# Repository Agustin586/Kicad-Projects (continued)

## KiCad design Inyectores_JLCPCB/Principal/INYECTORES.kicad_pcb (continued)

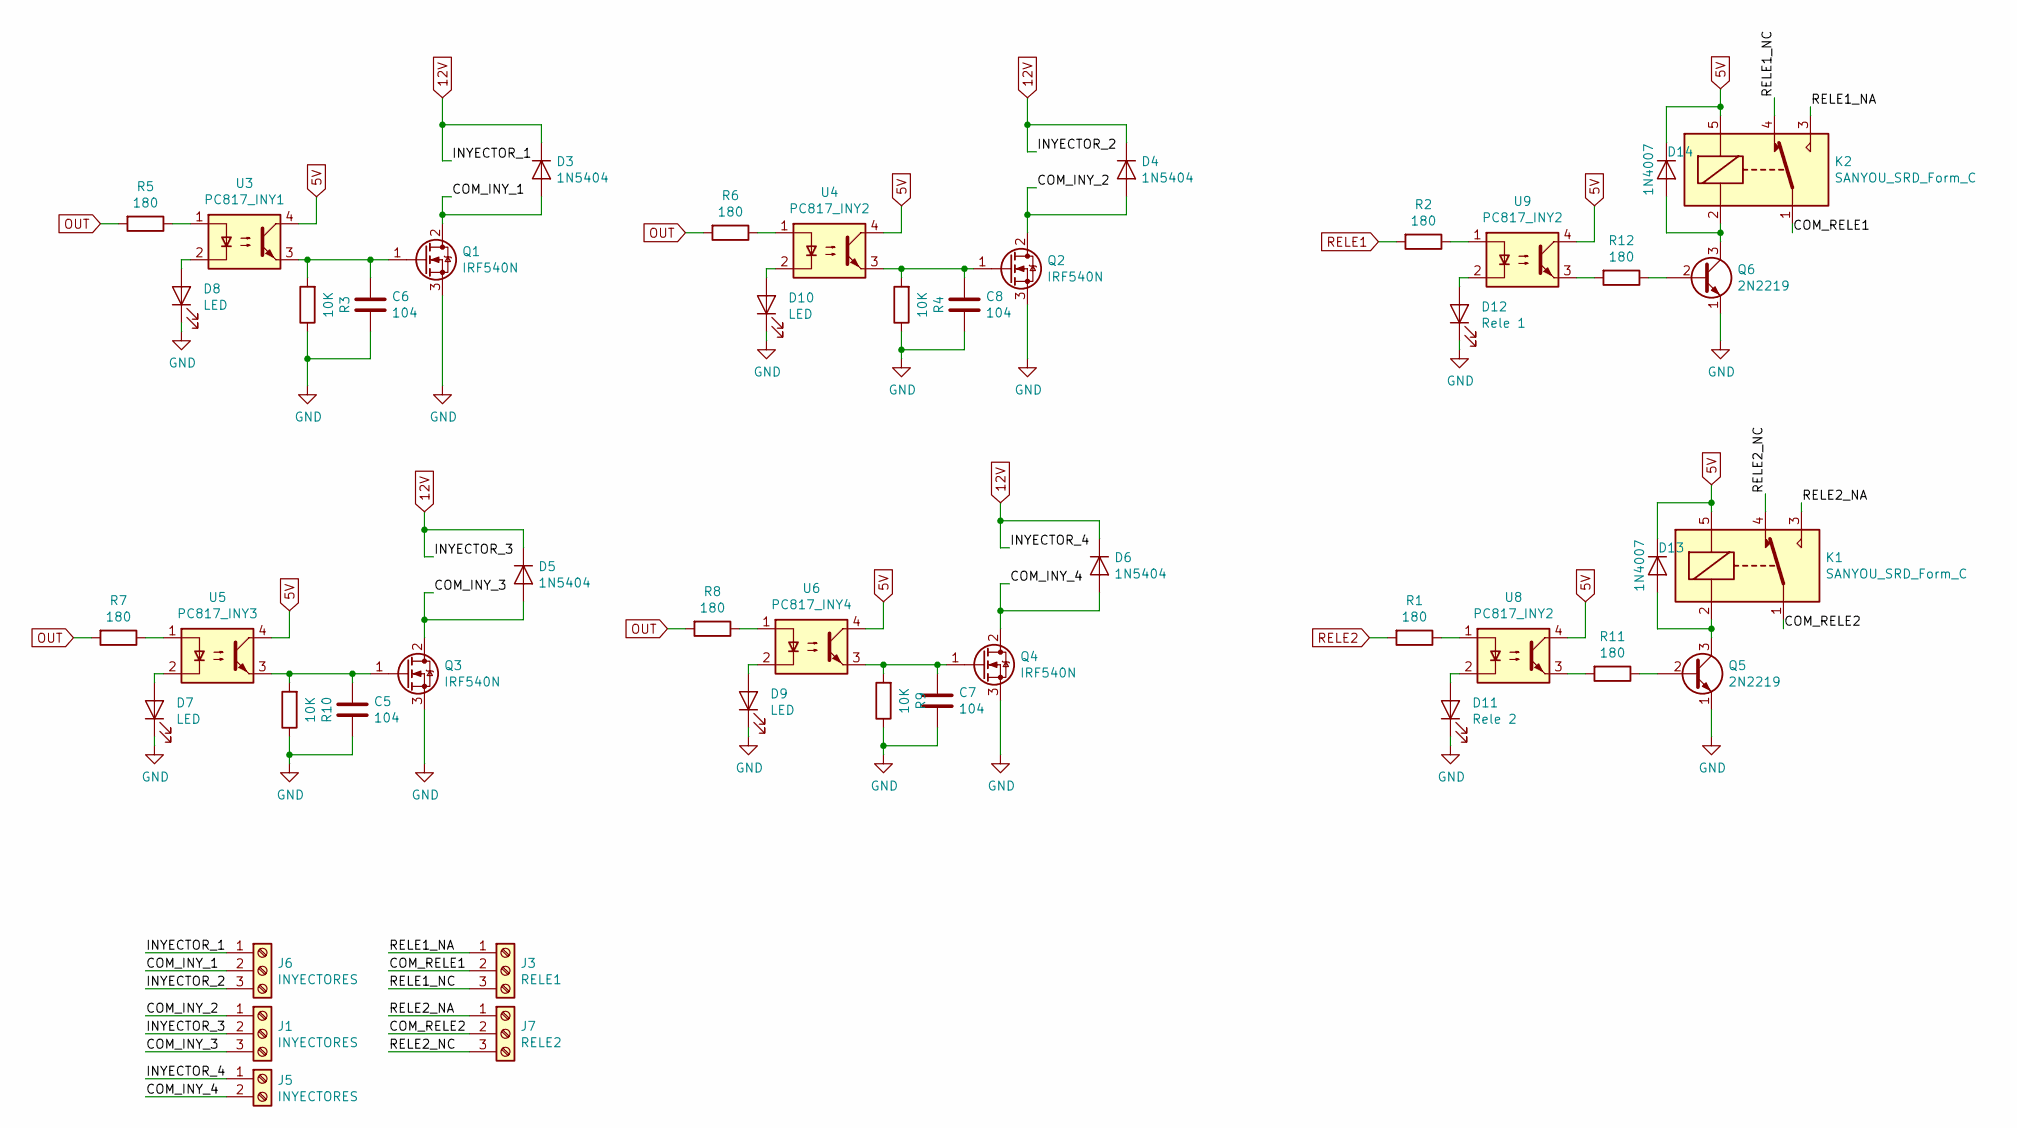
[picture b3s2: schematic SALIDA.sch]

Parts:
C5, C6, C7, C8: 104; C_Disc_D3.4mm_W2.1mm_P2.50mm
D3, D4, D5, D6: 1N5404; D_DO-201AD_P15.24mm_Horizontal
D7, D8, D9, D10: LED; LED_0805_2012Metric
D11: Rele 2; LED_0805_2012Metric
D12: Rele 1; LED_0805_2012Metric
D13, D14: 1N4007; D_DO-41_SOD81_P10.16mm_Horizontal
J1, J6: INYECTORES; TerminalBlock_Phoenix_PT-1,5-3-5.0-H_1x03_P5.00mm_Horizontal
J3: RELE1; TerminalBlock_Phoenix_PT-1,5-3-5.0-H_1x03_P5.00mm_Horizontal
J5: INYECTORES; TerminalBlock_Phoenix_PT-1,5-2-5.0-H_1x02_P5.00mm_Horizontal
J7: RELE2; TerminalBlock_Phoenix_PT-1,5-3-5.0-H_1x03_P5.00mm_Horizontal
K1, K2: SANYOU_SRD_Form_C; Relay_SPDT_SANYOU_SRD_Series_Form_C
Q1, Q2, Q3, Q4: IRF540N; TO-220-3_Vertical
Q5, Q6: 2N2219; TO-92_Inline
R1, R2, R5, R6, R7, R8, R11, R12: 180; R_Axial_DIN0207_L6.3mm_D2.5mm_P10.16mm_Horizontal
R3, R4, R9, R10: 10K; R_Axial_DIN0207_L6.3mm_D2.5mm_P10.16mm_Horizontal
U3: PC817_INY1; DIP-4_W7.62mm_LongPads
U4, U8, U9: PC817_INY2; DIP-4_W7.62mm_LongPads
U5: PC817_INY3; DIP-4_W7.62mm_LongPads
U6: PC817_INY4; DIP-4_W7.62mm_LongPads

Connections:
5V: D13.1 (K), D14.1 (K), K1.5, K2.5, U3.4, U4.4, U5.4, U6.4, U8.4, U9.4; also elsewhere on the board
/SALIDA/COM_INY_1: D3.2 (A), J6.2, Q1.2 (D)
/SALIDA/COM_INY_4: D6.2 (A), J5.2, Q4.2 (D)
/SALIDA/COM_RELE1: J3.2, K2.1
/SALIDA/COM_RELE2: J7.2, K1.1
/SALIDA/RELE1_NA: J3.1, K2.3
/SALIDA/RELE1_NC: J3.3, K2.4
/SALIDA/RELE2_NA: J7.1, K1.3
/SALIDA/RELE2_NC: J7.3, K1.4
unnamed: C5.1, Q3.1 (G), R10.2, U5.3
unnamed: C6.1, Q1.1 (G), R3.2, U3.3
unnamed: C7.1, Q4.1 (G), R9.2, U6.3
unnamed: C8.1, Q2.1 (G), R4.2, U4.3
unnamed 30: D7.2 (A), U5.2; also elsewhere on the board
unnamed: D10.2 (A), U4.2
unnamed: D11.2 (A), U8.2
unnamed: D12.2 (A), U9.2
unnamed: D13.2 (A), K1.2, Q5.3 (C)
unnamed: D14.2 (A), K2.2, Q6.3 (C)
unnamed: Q5.2 (B), R11.1
unnamed: Q6.2 (B), R12.1
unnamed: R1.1, U8.1
unnamed: R5.1, U3.1
unnamed: R6.1, U4.1
unnamed: R7.1, U5.1
unnamed: R8.1, U6.1
unnamed: R11.2, U8.3
unnamed: R12.2, U9.3
OUT: R5.2, R6.2, R7.2, R8.2; also elsewhere on the board
RELE1: R2.2; also elsewhere on the board
RELE2: R1.2; also elsewhere on the board

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
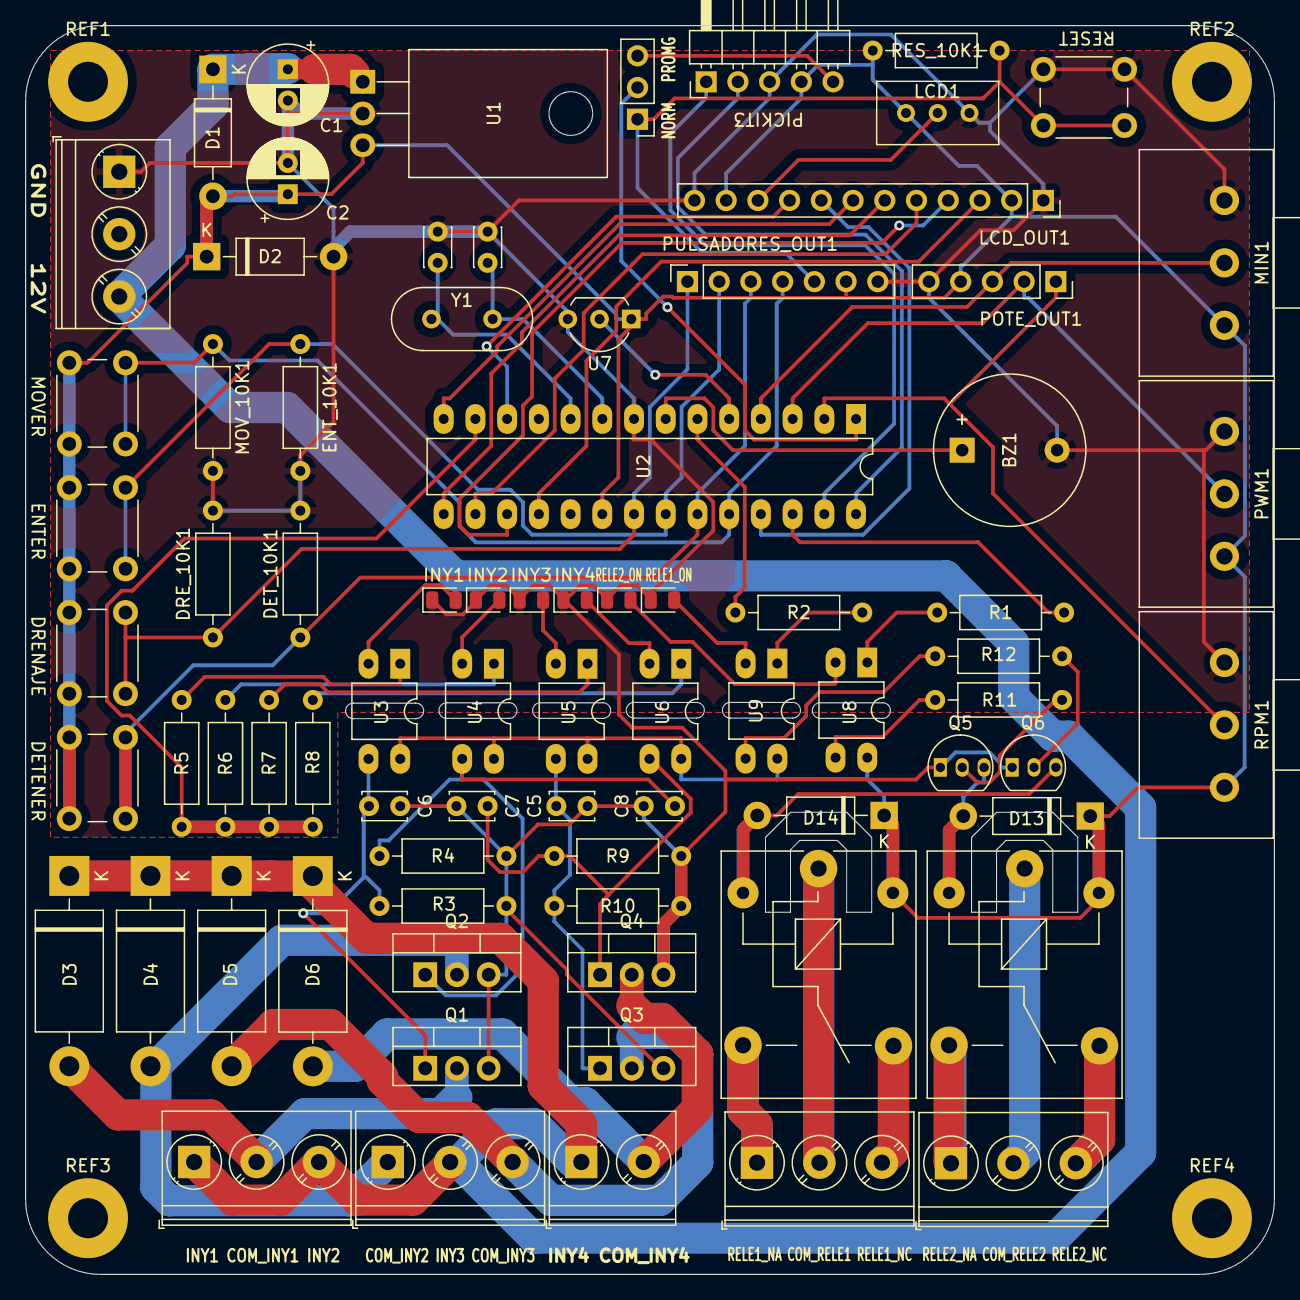
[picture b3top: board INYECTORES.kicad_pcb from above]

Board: 2 copper layers, 100.0 x 100.0 mm, 82 parts (0 on the bottom side), 62 nets.

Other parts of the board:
C1: 470uf/50v; CP_Radial_D6.3mm_P2.50mm
C2: 100uf/50v; CP_Radial_D6.3mm_P2.50mm
D1, D2: 1N4007; D_DO-41_SOD81_P10.16mm_Horizontal
J4: ENTRADA_CIRCUITO; TerminalBlock_Phoenix_PT-1,5-3-5.0-H_1x03_P5.00mm_Horizontal
REF1, REF2, REF3, REF4: MountingHole_3.2mm_M3_Pad
U1: L7805; TO-220-3_Horizontal_TabDown

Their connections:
5V: C2.1, D1.2, D2.1, U1.3; also elsewhere on the board

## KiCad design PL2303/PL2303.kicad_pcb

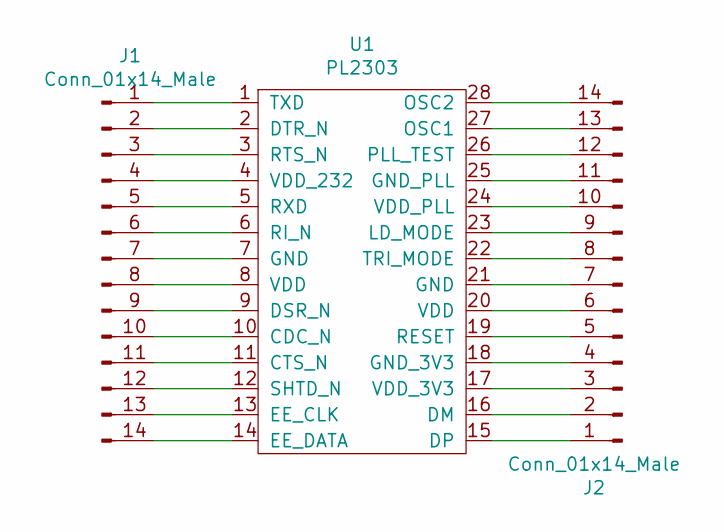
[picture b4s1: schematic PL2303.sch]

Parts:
J1, J2: Conn_01x14_Male; PinHeader_1x14_P2.54mm_Vertical
U1: PL2303; SOIC-28W_7.5x18.7mm_P1.27mm

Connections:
unnamed: J1.1, U1.1 (TXD)
unnamed: J1.2, U1.2 (DTR_N)
unnamed: J1.3, U1.3 (RTS_N)
unnamed: J1.4, U1.4 (VDD_232)
unnamed: J1.5, U1.5 (RXD)
unnamed: J1.6, U1.6 (RI_N)
unnamed: J1.7, U1.7 (GND)
unnamed: J1.8, U1.8 (VDD)
unnamed: J1.9, U1.9 (DSR_N)
unnamed: J1.10, U1.10 (CDC_N)
unnamed: J1.11, U1.11 (CTS_N)
unnamed: J1.12, U1.12 (SHTD_N)
unnamed: J1.13, U1.13 (EE_CLK)
unnamed: J1.14, U1.14 (EE_DATA)
unnamed: J2.1, U1.15 (DP)
unnamed: J2.2, U1.16 (DM)
unnamed: J2.3, U1.17 (VDD_3V3)
unnamed: J2.4, U1.18 (GND_3V3)
unnamed: J2.5, U1.19 (RESET)
unnamed: J2.6, U1.20 (VDD)
unnamed: J2.7, U1.21 (GND)
unnamed: J2.8, U1.22 (TRI_MODE)
unnamed: J2.9, U1.23 (LD_MODE)
unnamed: J2.10, U1.24 (VDD_PLL)
unnamed: J2.11, U1.25 (GND_PLL)
unnamed: J2.12, U1.26 (PLL_TEST)
unnamed: J2.13, U1.27 (OSC1)
unnamed: J2.14, U1.28 (OSC2)

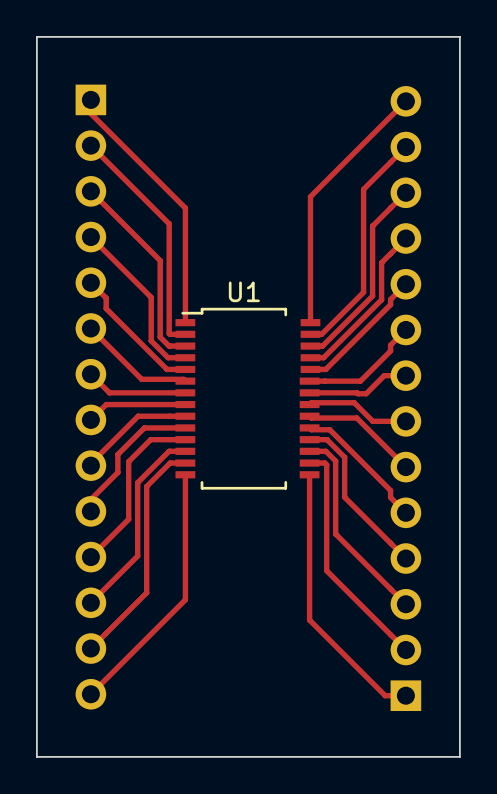
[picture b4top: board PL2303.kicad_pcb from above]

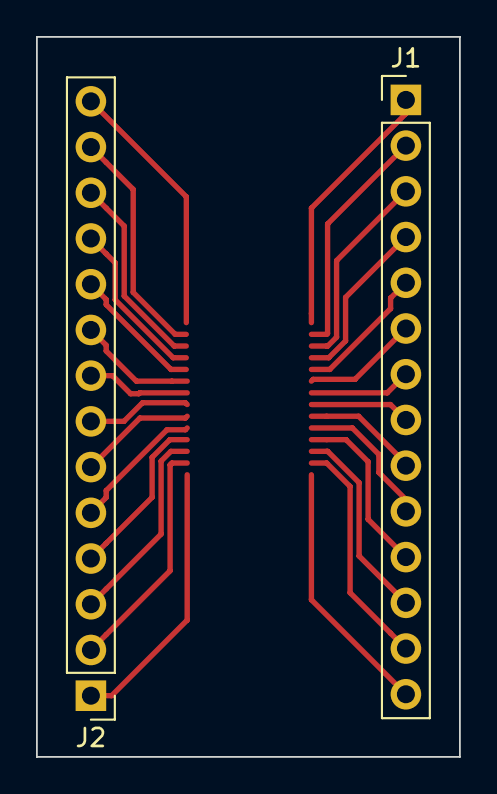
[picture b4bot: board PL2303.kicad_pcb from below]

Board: 2 copper layers, 23.5 x 40.0 mm, 3 parts (2 on the bottom side), 28 nets.

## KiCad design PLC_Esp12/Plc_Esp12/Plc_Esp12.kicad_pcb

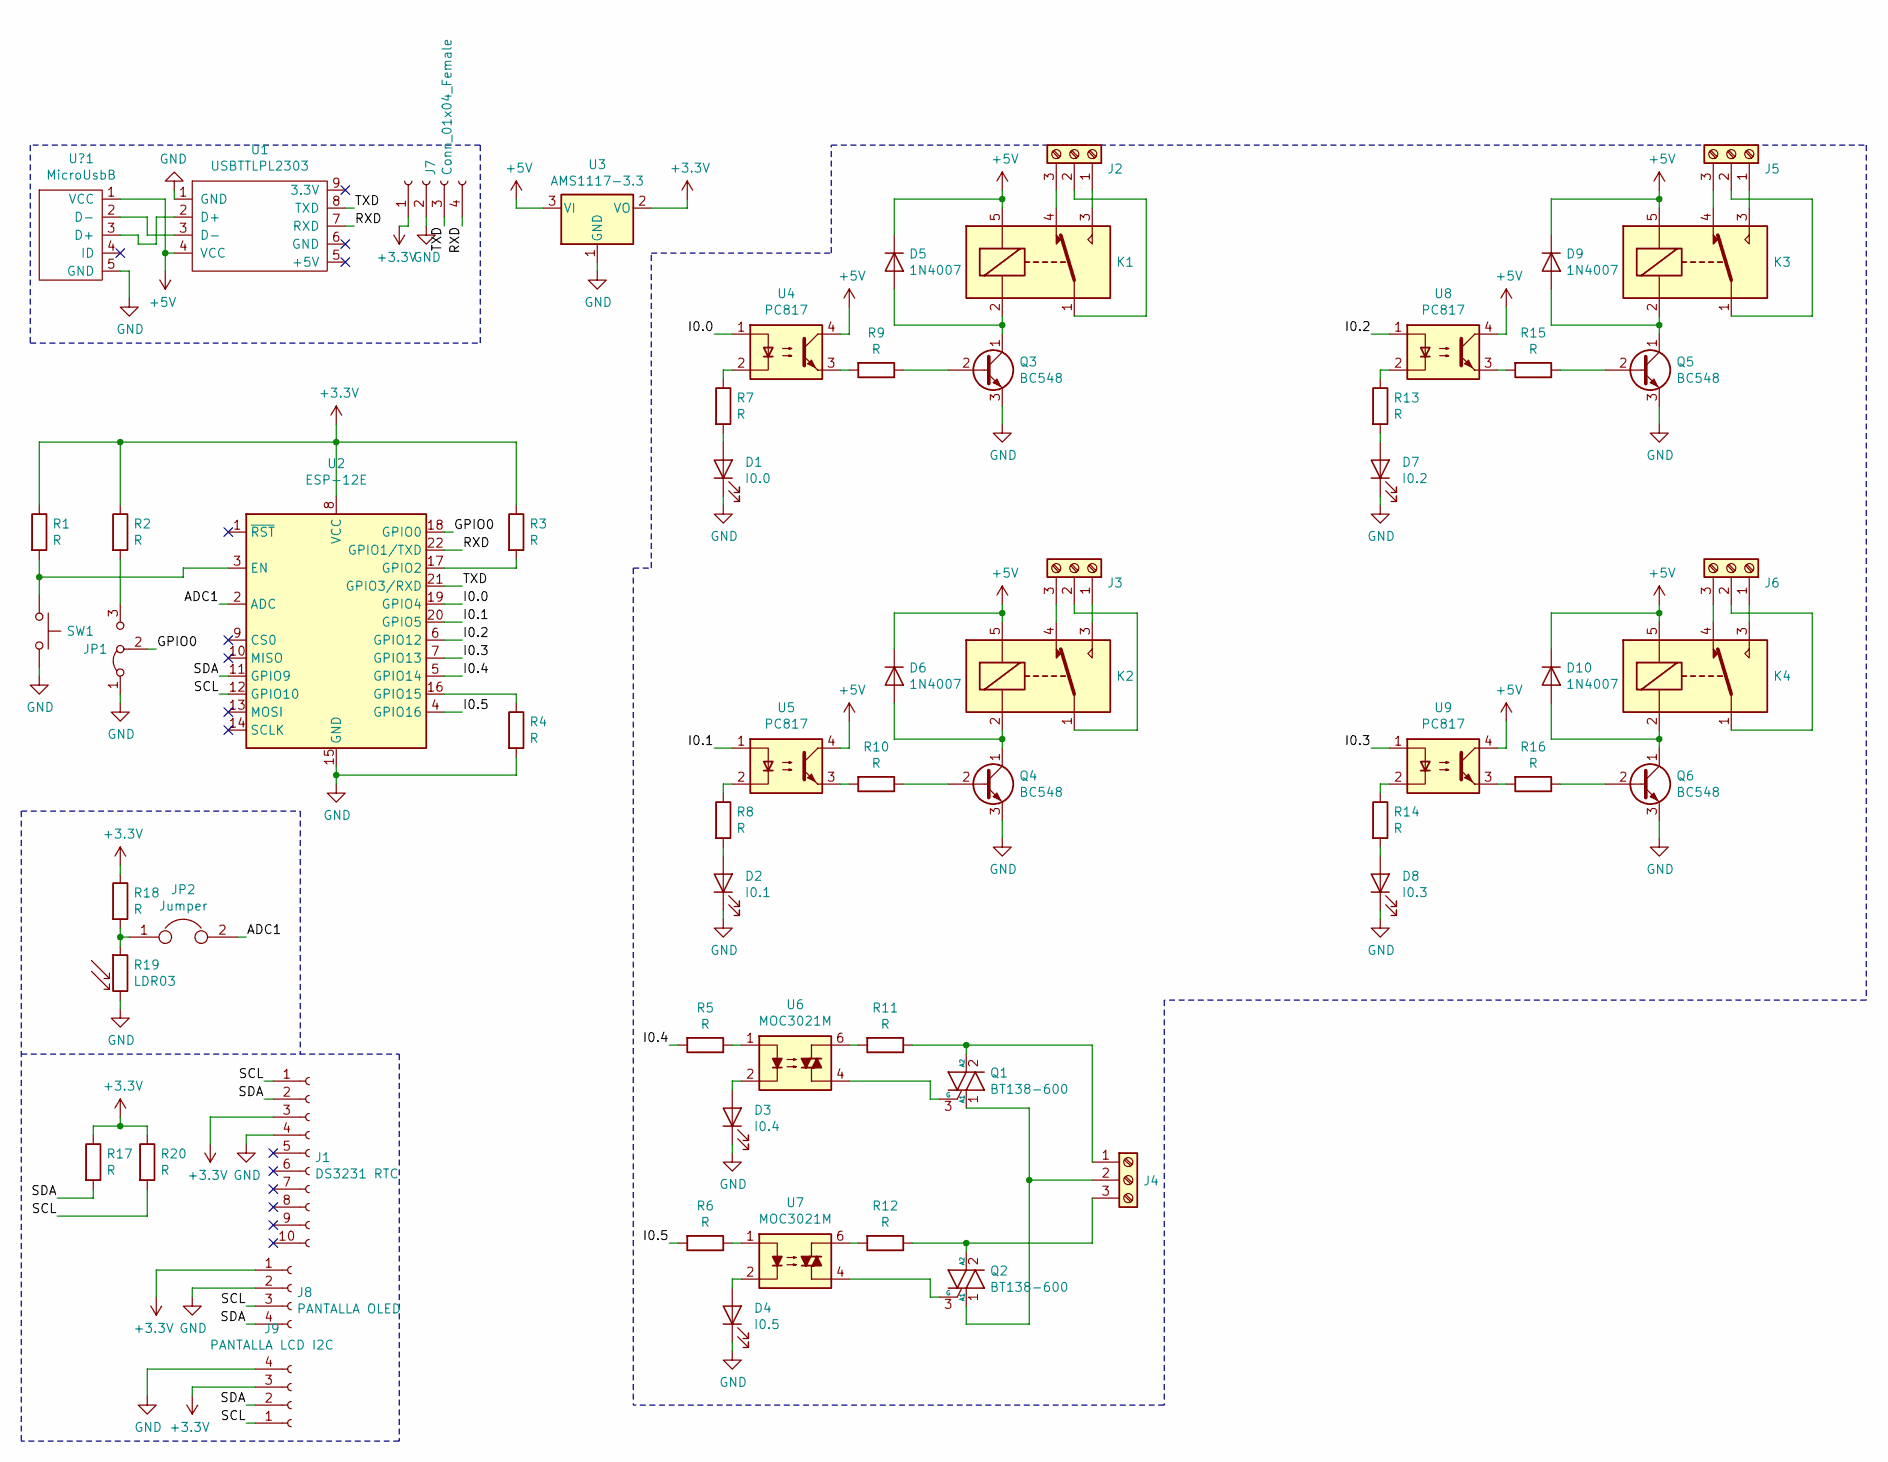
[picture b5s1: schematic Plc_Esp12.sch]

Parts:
D1: I0.0; LED_0805_2012Metric
D2: I0.1; LED_0805_2012Metric
D3: I0.4; LED_0805_2012Metric
D4: I0.5; LED_0805_2012Metric
D5, D6, D9, D10: 1N4007; D_DO-41_SOD81_P10.16mm_Horizontal
D7: I0.2; LED_0805_2012Metric
D8: I0.3; LED_0805_2012Metric
J1: DS3231 RTC; DS3231_Shield
J2, J3, J4, J5, J6: Screw_Terminal_01x03; TerminalBlock_Phoenix_PT-1,5-3-5.0-H_1x03_P5.00mm_Horizontal
J7: Conn_01x04_Female; PinSocket_1x04_P2.54mm_Vertical
J8: PANTALLA OLED; 128x64OLED
J9: PANTALLA LCD I2C; PinSocket_1x04_P2.54mm_Horizontal
JP1: Jumper_3_Bridged12; PinHeader_1x03_P2.54mm_Vertical
JP2: Jumper; PinHeader_1x02_P2.54mm_Vertical
K1, K2, K3, K4: SANYOU_SRD_Form_C; Relay_SPDT_SANYOU_SRD_Series_Form_C
Q1, Q2: BT138-600; TO-220-3_Vertical
Q3, Q4, Q5, Q6: BC548; TO-92_Inline_Wide
R1, R2, R3, R4, R5, R6, R7, R8, R9, R10, R11, R12, R13, R14, R15, R16, R17, R18, R20: R; R_Axial_DIN0207_L6.3mm_D2.5mm_P10.16mm_Horizontal
R19: LDR03; R_LDR_10x8.5mm_P7.6mm_Vertical
SW1: SW_Push; SW_PUSH_6mm
U1: USBTTLPL2303; PL2303USBTTL
U2: ESP-12E
U3: AMS1117-3.3; SOT-223-3_TabPin2
U4, U5, U8, U9: PC817; DIP-4_W7.62mm_LongPads
U6, U7: MOC3021M; DIP-6_W7.62mm_LongPads
U?1: MicroUsbB; Conn_USBmicro-B_ebay-side_TH

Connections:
+3V3: J1.3, J7.1, J8.1, J9.3, R1.1, R2.1, R3.1, R17.1, R18.1, R20.1, U2.8 (VCC), U3.2 (VO)
+5V: D5.1 (K), D6.1 (K), D9.1 (K), D10.1 (K), K1.5, K2.5, K3.5, K4.5, U1.4 (VCC), U3.3 (VI), U4.4, U5.4, U8.4, U9.4, U?1.1 (VCC)
/ADC1: JP2.2, U2.2 (ADC)
/GPIO0: JP1.2 (C), U2.18 (GPIO0)
/I0.0: U2.19 (GPIO4), U4.1
/I0.1: U2.20 (GPIO5), U5.1
/I0.2: U2.6 (GPIO12), U8.1
/I0.3: U2.7 (GPIO13), U9.1
/I0.4: R5.2, U2.5 (GPIO14)
/I0.5: R6.2, U2.4 (GPIO16)
/RXD: J7.4, U1.7 (RXD), U2.22 (GPIO1/TXD)
/SCL: J1.1, J8.3, J9.1, R20.2, U2.12 (GPIO10)
/SDA: J1.2, J8.4, J9.2, R17.2, U2.11 (GPIO9)
/TXD: J7.3, U1.8 (TXD), U2.21 (GPIO3/RXD)
GND: D1.1 (K), D2.1 (K), D3.1 (K), D4.1 (K), D7.1 (K), D8.1 (K), J1.4, J7.2, J8.2, J9.4, JP1.1 (A), Q3.3 (E), Q4.3 (E), Q5.3 (E), Q6.3 (E), R4.2, R19.2, SW1.2, U1.1 (GND), U2.15 (GND), U3.1 (GND), U?1.5 (GND)
unnamed: D1.2 (A), R7.2
unnamed: D2.2 (A), R8.2
unnamed: D3.2 (A), U6.2
unnamed: D4.2 (A), U7.2
unnamed: D5.2 (A), K1.2, Q3.1 (C)
unnamed: D6.2 (A), K2.2, Q4.1 (C)
unnamed: D7.2 (A), R13.2
unnamed: D8.2 (A), R14.2
unnamed: D9.2 (A), K3.2, Q5.1 (C)
unnamed: D10.2 (A), K4.2, Q6.1 (C)
unnamed: J2.1, K1.3
unnamed: J2.2, K1.1
unnamed: J2.3, K1.4
unnamed: J3.1, K2.3
unnamed: J3.2, K2.1
unnamed: J3.3, K2.4
unnamed: J4.1, Q1.2 (A2), R11.1
unnamed: J4.2, Q1.1 (A1), Q2.1 (A1)
unnamed: J4.3, Q2.2 (A2), R12.1
unnamed: J5.1, K3.3
unnamed: J5.2, K3.1
unnamed: J5.3, K3.4
unnamed: J6.1, K4.3
unnamed: J6.2, K4.1
unnamed: J6.3, K4.4
unnamed: JP1.3 (B), R2.2
unnamed: JP2.1, R18.2, R19.1
unnamed: Q1.3 (G), U6.4
unnamed: Q2.3 (G), U7.4
unnamed: Q3.2 (B), R9.1
unnamed: Q4.2 (B), R10.1
unnamed: Q5.2 (B), R15.1
unnamed: Q6.2 (B), R16.1
unnamed: R1.2, SW1.1, U2.3 (EN)
unnamed: R3.2, U2.17 (GPIO2)
unnamed: R4.1, U2.16 (GPIO15)
unnamed: R5.1, U6.1
unnamed: R6.1, U7.1
unnamed: R7.1, U4.2
unnamed: R8.1, U5.2
unnamed: R9.2, U4.3
unnamed: R10.2, U5.3
unnamed: R11.2, U6.6
unnamed: R12.2, U7.6
unnamed: R13.1, U8.2
unnamed: R14.1, U9.2
unnamed: R15.2, U8.3
unnamed: R16.2, U9.3
unnamed: U1.2 (D+), U?1.3 (D+)
unnamed: U1.3 (D-), U?1.2 (D-)

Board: 2 copper layers, 66 parts (1 on the bottom side), 65 nets, no tracks yet.

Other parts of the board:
REF1, REF2, REF3, REF4: MountingHole_3.2mm_M3_Pad

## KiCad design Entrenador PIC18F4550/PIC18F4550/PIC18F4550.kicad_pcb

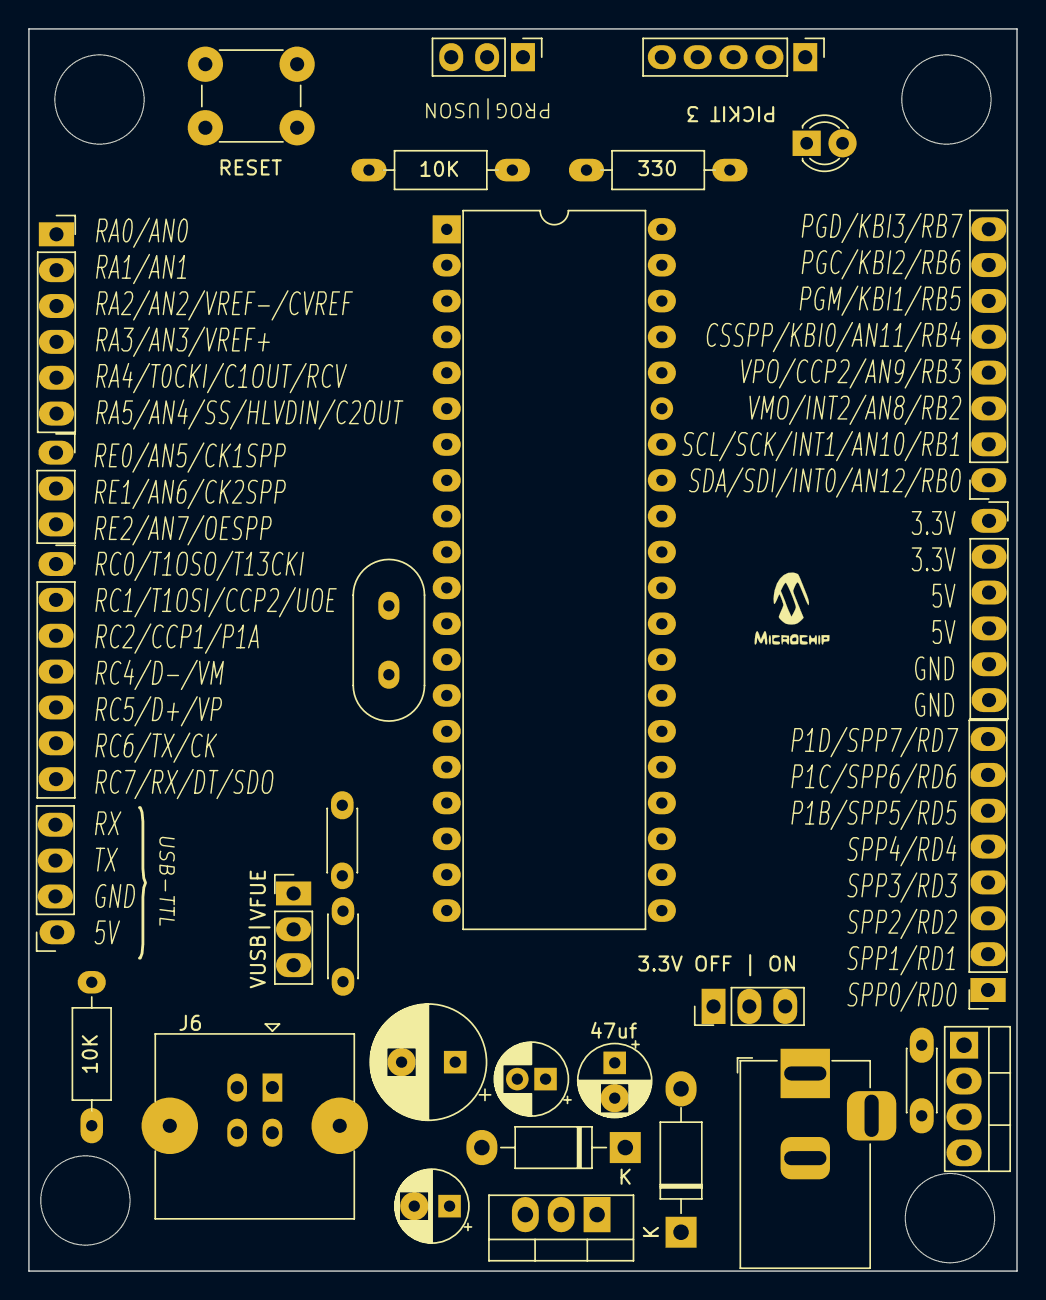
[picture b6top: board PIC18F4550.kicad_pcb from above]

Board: 2 copper layers, 70.0 x 88.0 mm, 31 parts (0 on the bottom side), 47 nets, no tracks yet.

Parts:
C1: 100nf; C_Disc_D4.3mm_W1.9mm_P5.00mm
C2: 10uf; CP_Radial_D5.0mm_P2.00mm
C3: 100uf; CP_Radial_D5.0mm_P2.50mm
C4: 470uf; CP_Radial_D8.0mm_P3.80mm
C5, C6: 15pf; C_Disc_D4.3mm_W1.9mm_P5.00mm
C7: 47uf; CP_Radial_D5.0mm_P2.50mm
D1, D2: 1N4007; D_DO-41_SOD81_P10.16mm_Horizontal
D3: ROJO; LED_D3.0mm
J1: Barrel_Jack_Switch; BarrelJack_Horizontal
J2: Alimenatciones; PinSocket_1x06_P2.54mm_Vertical
J3: PICKIT; PinHeader_1x05_P2.54mm_Vertical
J5: Conn_01x03_Male; PinHeader_1x03_P2.54mm_Vertical
J6: USB_B; USB_B_TE_5787834_Vertical
J7: PORTE; PinSocket_1x03_P2.54mm_Vertical
J8: PORTB; PinSocket_1x08_P2.54mm_Vertical
J9: PORTD; PinSocket_1x08_P2.54mm_Vertical
J10: PORTA; PinSocket_1x06_P2.54mm_Vertical
J11: PORTC; PinSocket_1x07_P2.54mm_Vertical
J12: UART_TTL; PinSocket_1x04_P2.54mm_Vertical
JP1: Alimentacion; PinHeader_1x03_P2.54mm_Vertical
JP2: PIN4_ON_OFF; PinHeader_1x03_P2.54mm_Vertical
R1: 330; R_Axial_DIN0207_L6.3mm_D2.5mm_P10.16mm_Horizontal
R2, R3: 10K; R_Axial_DIN0207_L6.3mm_D2.5mm_P10.16mm_Horizontal
SW1: RESET; SW_PUSH_6mm
U1: KA378R33; TO-220-4_Vertical
U2: L7805; TO-220-3_Vertical
U3: PIC18F4550-IP; DIP-40_W15.24mm
Y1: Crystal; Crystal_HC49-4H_Vertical

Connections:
3.3V: C1.1, J2.1, J2.2, U1.2
5V: C2.1, J2.3, J2.4, J3.2, J12.1, JP1.2, JP2.3, R1.1, R2.1, U1.1, U3.11, U3.32
/MCLR: J5.2, U3.1
/OSC1: C5.1, U3.13, Y1.2
/OSC2: C6.1, U3.14, Y1.1
/PROM_MCLR: J3.1, J5.1
/PUSH_RESET: J5.3, R2.2, SW1.2
/RA0: J10.1, U3.2
/RA1: J10.2, U3.3
/RA2: J10.3, U3.4
/RA3: J10.4, U3.5
/RA4: J10.5, U3.6
/RA5: J10.6, U3.7
/RB0: J8.1, U3.33
/RB1: J8.2, U3.34
/RB2: J8.3, U3.35
/RB3: J8.4, U3.36
/RB4: J8.5, U3.37
/RB5: J8.6, U3.38
/RB6: J3.5, J8.7, U3.39
/RB7: J3.4, J8.8, U3.40
/RC0: J11.1, U3.15
/RC1: J11.2, U3.16
/RC2: J11.3, U3.17
/RC4: J6.2, J11.4, U3.23
/RC5: J6.3, J11.5, U3.24
/RC6: J11.6, J12.3, U3.25
/RC7: J11.7, J12.4, U3.26
/RD0: J9.1, U3.19
/RD1: J9.2, U3.20
/RD2: J9.3, U3.21
/RD3: J9.4, U3.22
/RD4: J9.5, U3.27
/RD5: J9.6, U3.28
/RD6: J9.7, U3.29
/RD7: J9.8, U3.30
/RE0: J7.1, U3.8
/RE1: J7.2, U3.9
/RE2: J7.3, U3.10
/VBUS: J6.1, JP1.3, R3.2
GND: C1.2, C2.2, C3.2, C4.2, C5.2, C6.2, C7.2, D3.1, J1.2, J1.3, J2.5, J2.6, J3.3, J6.4, J6.5, J12.2, JP2.1, R3.1, SW1.1, U1.3, U2.2, U3.12, U3.31
unnamed: C3.1, D1.2, JP1.1, U2.3
unnamed: C4.1, D1.1, D2.1, U2.1
unnamed: C7.1, U3.18
unnamed: D3.2, R1.2
unnamed: JP2.2, U1.4
VCC: D2.2, J1.1

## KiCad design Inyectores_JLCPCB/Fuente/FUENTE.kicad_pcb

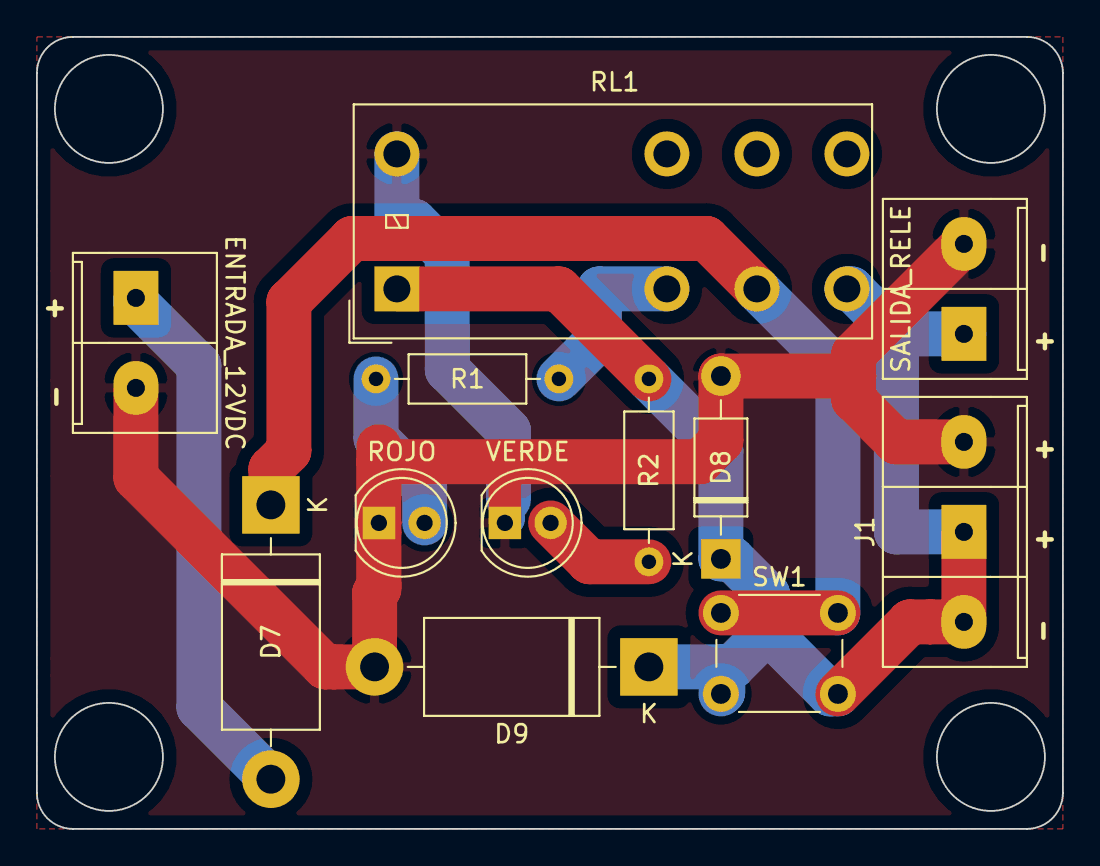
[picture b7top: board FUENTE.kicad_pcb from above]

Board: 2 copper layers, 57.0 x 44.0 mm, 12 parts (0 on the bottom side), 7 nets.

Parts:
D7, D9: 1N5408; D_DO-201AD_P15.24mm_Horizontal
D8: 1N4007; D_DO-41_SOD81_P10.16mm_Horizontal
ENTRADA_12VDC: Screw_Terminal_01x02; bornera_tornillos_1x02
J1: Screw_Terminal_01x03; bornera_tornillos_1x03
R1, R2: 440; R_Axial_DIN0207_L6.3mm_D2.5mm_P10.16mm_Horizontal
RL1: JW2; Relay_DPDT_Panasonic_JW2
ROJO: LED; LED_D5.0mm
SALIDA_RELE: Screw_Terminal_01x02; bornera_tornillos_1x02
SW1: SW_Push; SW_PUSH_6mm
VERDE: LED; LED_D5.0mm

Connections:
/GND_RELE: D8.2, D9.2, ENTRADA_12VDC.2, J1.3, RL1.8, ROJO.1, SALIDA_RELE.2, VERDE.1
unnamed: D7.1, RL1.3, SW1.1
unnamed: D7.2, ENTRADA_12VDC.1
unnamed: D8.1, D9.1, J1.1, J1.2, R2.1, RL1.1, RL1.4, SALIDA_RELE.1, SW1.2
unnamed: R1.1, RL1.2
unnamed: R1.2, ROJO.2
unnamed: R2.2, VERDE.2

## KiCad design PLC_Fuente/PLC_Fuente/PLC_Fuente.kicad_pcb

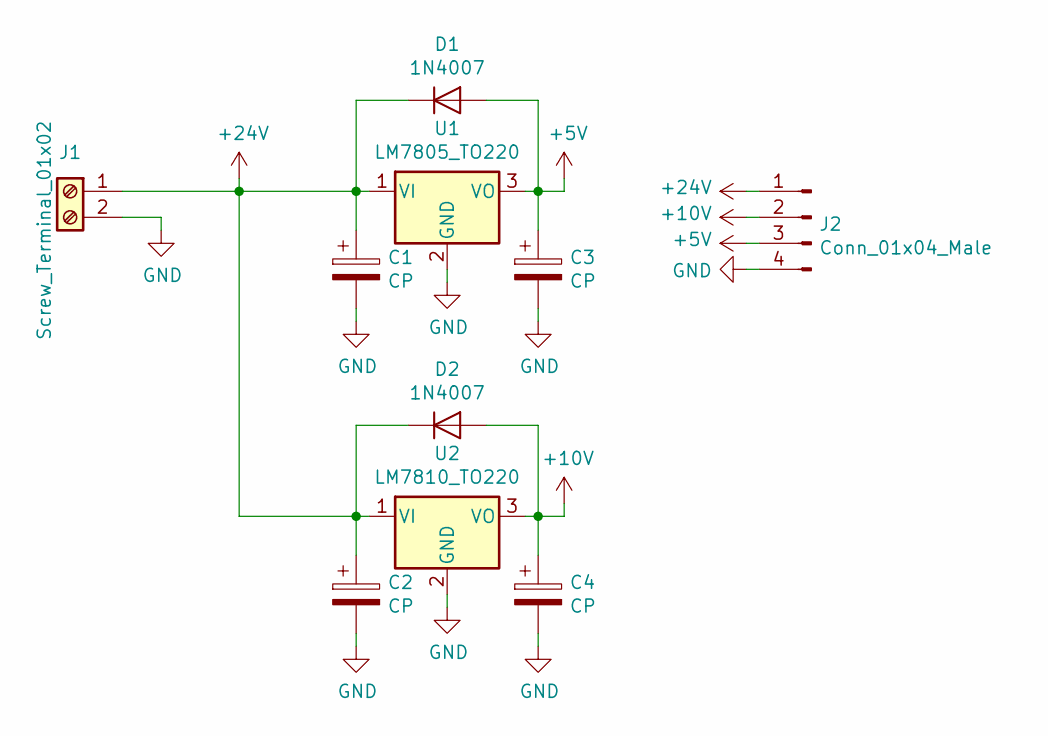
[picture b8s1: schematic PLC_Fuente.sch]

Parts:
C1, C2, C3, C4: CP; CP_Radial_D8.0mm_P3.50mm
D1, D2: 1N4007; D_DO-41_SOD81_P10.16mm_Horizontal
J1: Screw_Terminal_01x02; TerminalBlock_Phoenix_PT-1,5-2-5.0-H_1x02_P5.00mm_Horizontal
J2: Conn_01x04_Male; PinHeader_1x04_P2.54mm_Vertical
U1: LM7805_TO220; TO-220-3_Horizontal_TabDown
U2: LM7810_TO220; TO-220-3_Horizontal_TabDown

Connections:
+5V: C3.1, D1.2 (A), J2.3, U1.3 (VO)
+10V: C4.1, D2.2 (A), J2.2, U2.3 (VO)
+24V: C1.1, C2.1, D1.1 (K), D2.1 (K), J1.1, J2.1, U1.1 (VI), U2.1 (VI)
GND: C1.2, C2.2, C3.2, C4.2, J1.2, J2.4, U1.2 (GND), U2.2 (GND)

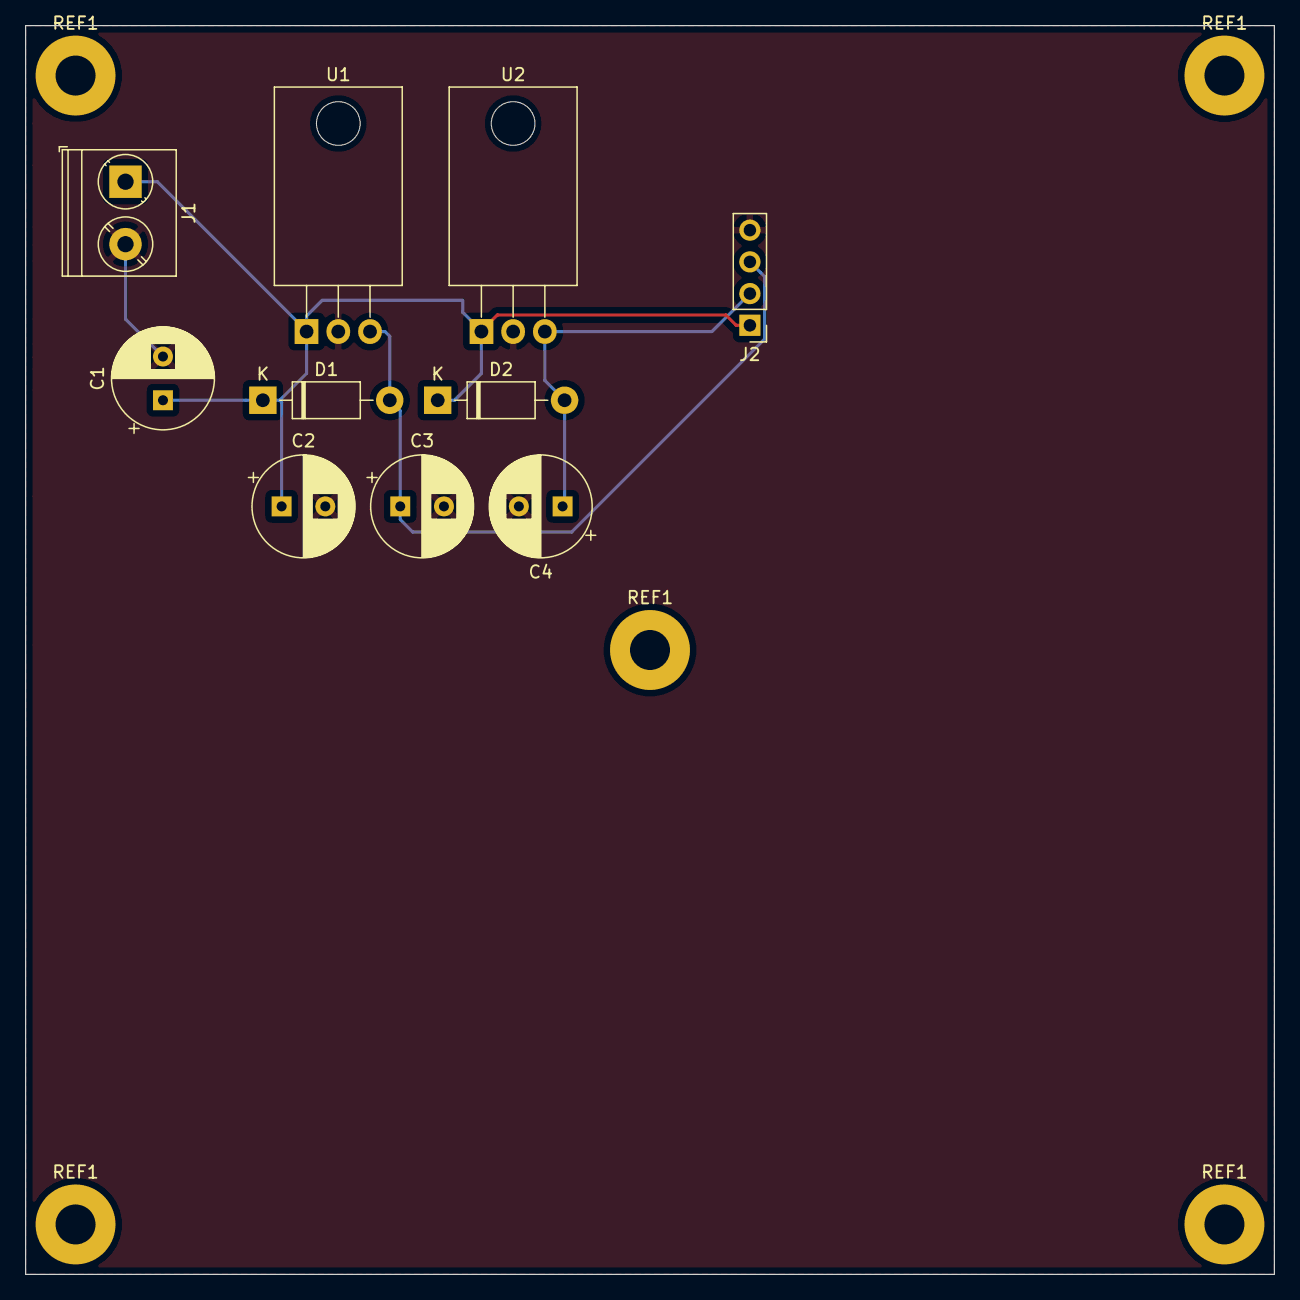
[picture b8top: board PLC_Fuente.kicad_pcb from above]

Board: 2 copper layers, 100.0 x 100.0 mm, 15 parts (0 on the bottom side), 4 nets.

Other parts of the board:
REF1, REF1#2, REF1#3, REF1#4, REF1#5: MountingHole_3.2mm_M3_Pad

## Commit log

2021-05-09 Primer commit
2021-08-26 Pcbs
2021-11-23 Cambios
2022-01-18 Nuevo Proyecto inyectores
2022-04-13 Actualizacion PCB
2022-07-25 Insoladora UV
2022-07-26 Insoladora
    Se realizo la pcb de la insoladora con dos reles.
2022-07-26 .
    .
2022-07-26 Insoladora UV
    Nueva carpeta
2022-08-01 Insoladora
    Se termino la pcb de 10x10 para la insoladora
2022-08-21 Insoladora
    Circuito Terminado
2023-08-18 Fte_Alimentacion
2023-08-27 Avance
